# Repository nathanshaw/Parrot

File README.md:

# Parrot
Repo for housing everything Parrot Bot. A mechatronic creature which borrows rhythmic motifs from the sonic environment to playback on a host of actuators.

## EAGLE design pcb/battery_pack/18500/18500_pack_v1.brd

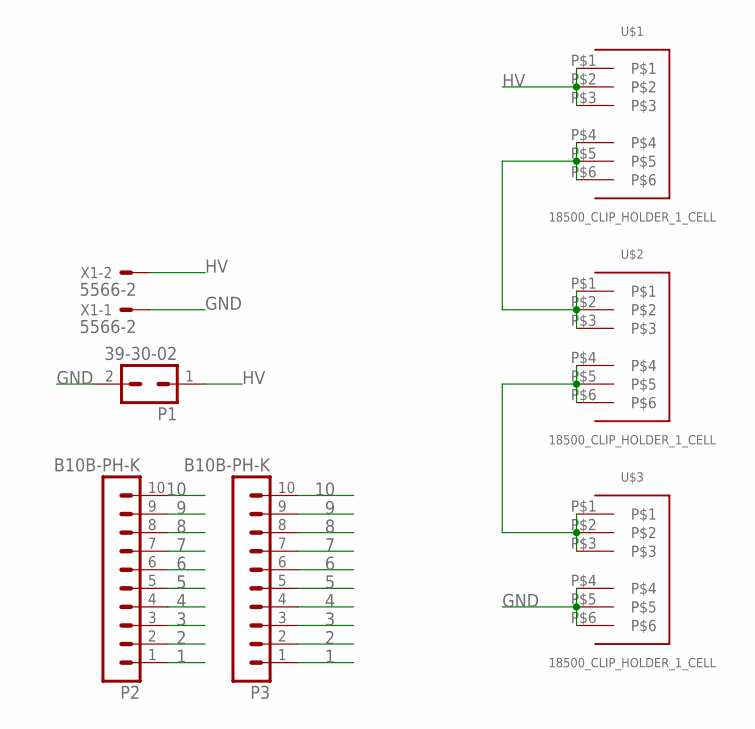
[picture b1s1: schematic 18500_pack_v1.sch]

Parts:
P1: 39-30-02; 39-30-?02?
P2, P3: B10B-PH-K
U$1, U$2, U$3: 18500_CLIP_HOLDER_1_CELL; 3PINBATTERY_CLIP_1_CELL_18500
X1: 5566-2

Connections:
1: P2.1, P3.1
2: P2.2, P3.2
3: P2.3, P3.3
4: P2.4, P3.4
5: P2.5, P3.5
6: P2.6, P3.6
7: P2.7, P3.7
8: P2.8, P3.8
9: P2.9, P3.9
10: P2.10, P3.10
GND: P1.2, U$3.P$4, U$3.P$5, U$3.P$6, X1.1
HV: P1.1, U$1.P$1, U$1.P$2, U$1.P$3, X1.2
unnamed: U$1.P$4, U$1.P$5, U$1.P$6, U$2.P$1, U$2.P$2, U$2.P$3
unnamed: U$2.P$4, U$2.P$5, U$2.P$6, U$3.P$1, U$3.P$2, U$3.P$3

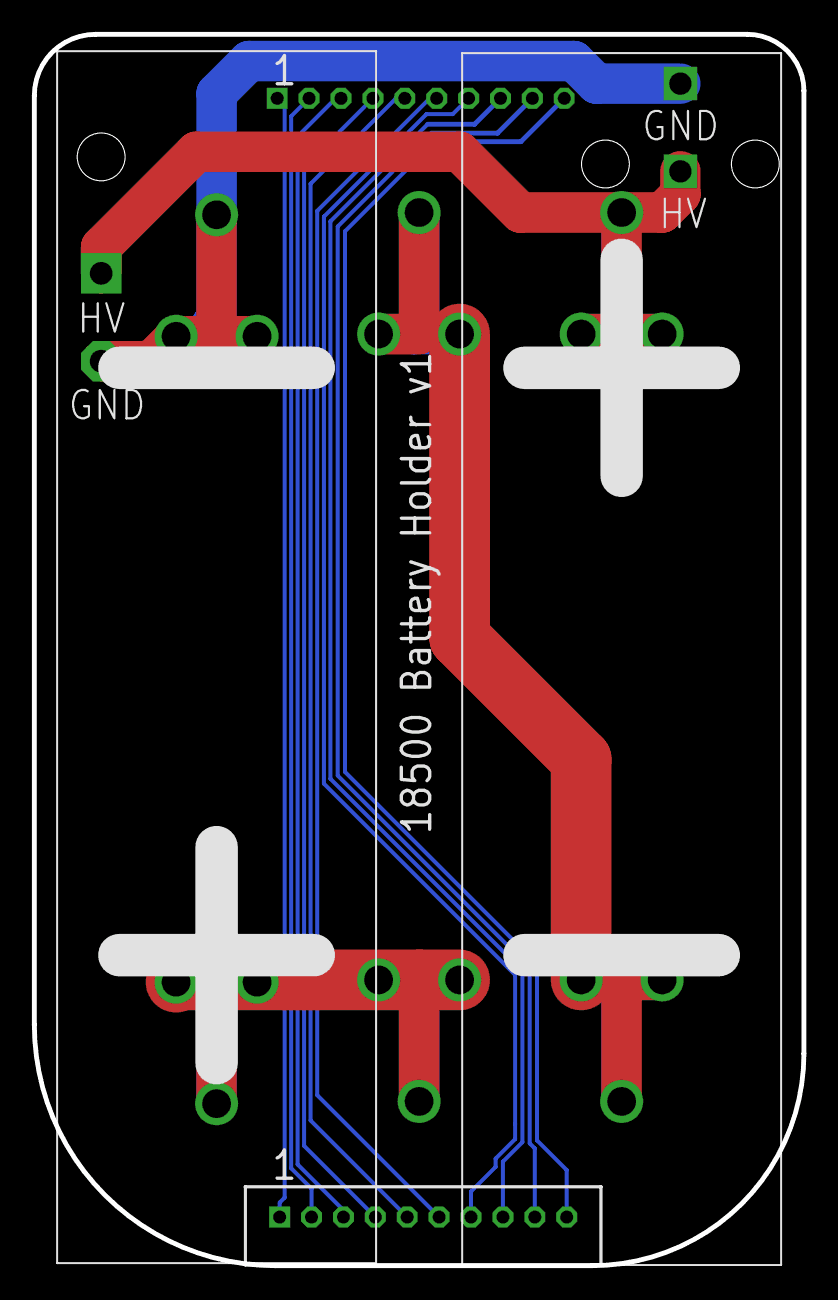
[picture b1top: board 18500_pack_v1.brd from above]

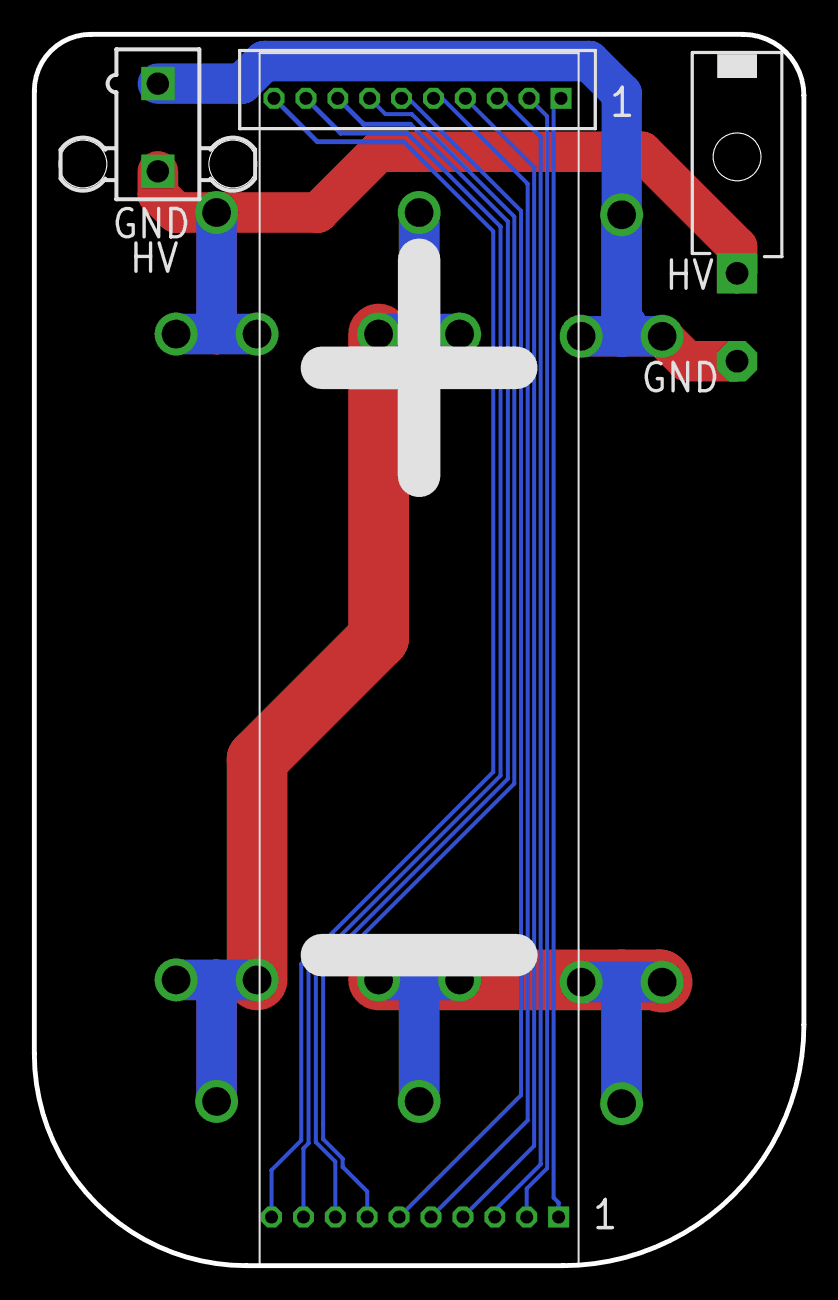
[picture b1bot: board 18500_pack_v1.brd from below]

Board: 2 copper layers, 48.3 x 77.2 mm, 7 parts (4 on the bottom side), 14 nets.

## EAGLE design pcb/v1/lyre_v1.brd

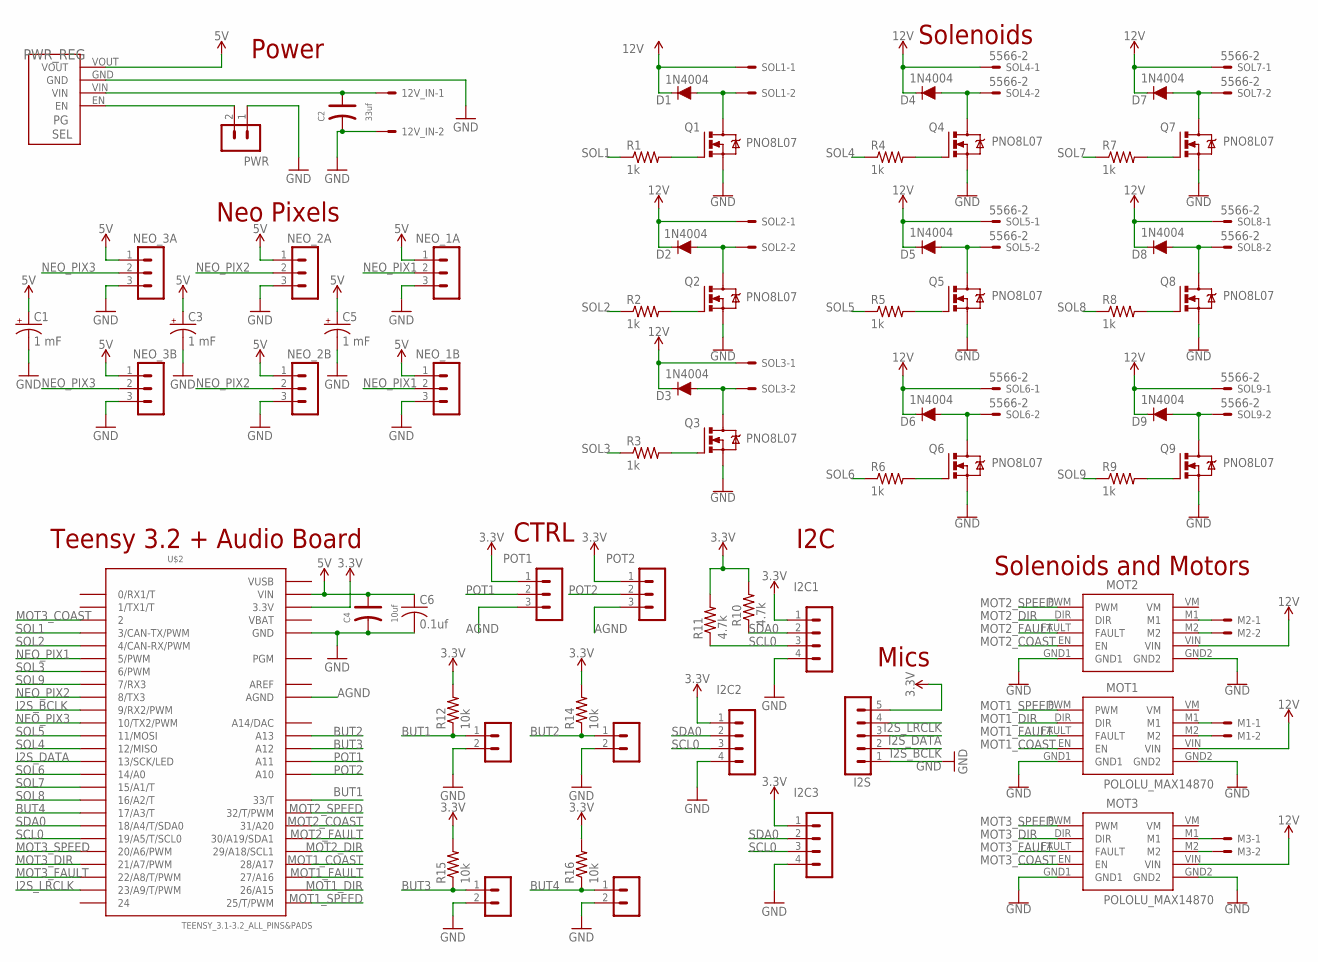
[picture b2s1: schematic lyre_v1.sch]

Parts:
12V_IN: 5566-2
BUT1, BUT2, BUT3, BUT4: B2B-PH-K
C1, C3, C5: 1 mF; UD-10X10_NICHICON
C2: 33uf; PC-D5.3MM
C4: 10uf; PC-D5.3MM
C6: 0.1uf; C2012
D1, D2, D3, D4, D5, D6, D7, D8, D9: 1N4004; DIOAD1138W86L465D235B
I2C1, I2C2, I2C3: B4B-PH-K
I2S: B5B-PH-K
M1, M2, M3: 5566-2
MOT1, MOT2, MOT3: POLOLU_MAX14870
NEO_1A, NEO_1B, NEO_2A, NEO_2B, NEO_3A, NEO_3B: B3B-PH-K
POT1, POT2: B3B-PH-K
PWR: B2B-PH-K
PWR_REG: S9V11F5S6CMA_MISSINIG_PINS; S9V11F3S5CMA_MISSING_PINS
Q1, Q2, Q3, Q4, Q5, Q6, Q7, Q8, Q9: PNO8L07; TO220BV
R1, R2, R3, R4, R5, R6, R7, R8, R9: 1k; R0805
R10, R11: 4.7k; R0805
R12, R14, R15, R16: 10k; R0805
SOL1, SOL2, SOL3, SOL4, SOL5, SOL6, SOL7, SOL8, SOL9: 5566-2
U$2: TEENSY_3.1-3.2_ALL_PINS&PADS; TEENSY_3.0-3.2_ALL_PINS_&_PADS

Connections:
3.3V: I2C1.1, I2C2.1, I2C3.1, I2S.5, POT1.1, POT2.1, R10.2, R11.2, R12.2, R14.2, R15.2, R16.2, U$2.3.3V, U$2.3.3V1 (3.3V), U$2.3.3V2 (3.3V)
5V: C1.+, C3.+, C4.+, C5.+, C6.1, NEO_1A.1, NEO_1B.1, NEO_2A.1, NEO_2B.1, NEO_3A.1, NEO_3B.1, PWR_REG.VOUT, U$2.VIN
12V: 12V_IN.1, C2.+, D1.2 (C), D2.2 (C), D3.2 (C), D4.2 (C), D5.2 (C), D6.2 (C), D7.2 (C), D8.2 (C), D9.2 (C), MOT1.VIN, MOT2.VIN, MOT3.VIN, PWR_REG.VIN, SOL1.1, SOL2.1, SOL3.1, SOL4.1, SOL5.1, SOL6.1, SOL7.1, SOL8.1, SOL9.1
AGND: POT1.3, POT2.3, U$2.AGND
AREF: U$2.AREF
BUT1: BUT1.1, R12.1, U$2.33 (33/T)
BUT2: BUT2.1, R14.1, U$2.A13
BUT3: BUT3.1, R15.1, U$2.A12
BUT4: BUT4.1, R16.1, U$2.17/A3 (17/A3/T)
GND: 12V_IN.2, BUT1.2, BUT2.2, BUT3.2, BUT4.2, C1.-, C2.-, C3.-, C4.-, C5.-, C6.2, I2C1.4, I2C2.4, I2C3.4, I2S.1, MOT1.GND1, MOT1.GND2, MOT2.GND1, MOT2.GND2, MOT3.GND1, MOT3.GND2, NEO_1A.3, NEO_1B.3, NEO_2A.3, NEO_2B.3, NEO_3A.3, NEO_3B.3, PWR.1, PWR_REG.GND, Q1.S, Q2.S, Q3.S, Q4.S, Q5.S, Q6.S, Q7.S, Q8.S, Q9.S, U$2.GND, U$2.GND1 (GND), U$2.GND2 (GND)
I2S_BCLK: I2S.2, U$2.9 (9/RX2/PWM)
I2S_DATA: I2S.3, U$2.13 (13/SCK/LED)
I2S_LRCLK: I2S.4, U$2.23/A9 (23/A9/T/PWM)
MOT1_COAST: MOT1.EN, U$2.28 (28/A17)
MOT1_DIR: MOT1.DIR, U$2.26 (26/A15)
MOT1_FAULT: MOT1.FAULT, U$2.27 (27/A16)
MOT1_SPEED: MOT1.PWM, U$2.25 (25/T/PWM)
MOT2_COAST: MOT2.EN, U$2.31 (31/A20)
MOT2_DIR: MOT2.DIR, U$2.29 (29/A18/SCL1)
MOT2_FAULT: MOT2.FAULT, U$2.30 (30/A19/SDA1)
MOT2_SPEED: MOT2.PWM, U$2.32 (32/T/PWM)
MOT3_COAST: MOT3.EN, U$2.2
MOT3_DIR: MOT3.DIR, U$2.21/A7 (21/A7/PWM)
MOT3_FAULT: MOT3.FAULT, U$2.22/A8 (22/A8/T/PWM)
MOT3_SPEED: MOT3.PWM, U$2.20/A6 (20/A6/PWM)
unnamed: Q5.G, R5.2
unnamed: D5.1 (A), Q5.D, SOL5.2
unnamed: M1.2, MOT1.M2
unnamed: Q6.G, R6.2
unnamed: Q2.G, R2.2
unnamed: D6.1 (A), Q6.D, SOL6.2
unnamed: D2.1 (A), Q2.D, SOL2.2
unnamed: M1.1, MOT1.M1
unnamed: PWR.2, PWR_REG.EN
unnamed: Q3.G, R3.2
unnamed: D3.1 (A), Q3.D, SOL3.2
unnamed: Q4.G, R4.2
unnamed: D4.1 (A), Q4.D, SOL4.2
unnamed: M3.2, MOT3.M2
unnamed: M3.1, MOT3.M1
unnamed: Q7.G, R7.2
unnamed: D7.1 (A), Q7.D, SOL7.2
unnamed: Q8.G, R8.2
unnamed: D8.1 (A), Q8.D, SOL8.2
unnamed: Q9.G, R9.2
unnamed: D9.1 (A), Q9.D, SOL9.2
unnamed: Q1.G, R1.2
unnamed: D1.1 (A), Q1.D, SOL1.2
unnamed: M2.2, MOT2.M2
unnamed: M2.1, MOT2.M1
NEO_PIX1: NEO_1A.2, NEO_1B.2, U$2.5 (5/PWM)
NEO_PIX2: NEO_2A.2, NEO_2B.2, U$2.8 (8/TX3)
NEO_PIX3: NEO_3A.2, NEO_3B.2, U$2.10 (10/TX2/PWM)
POT1: POT1.2, U$2.A11
POT2: POT2.2, U$2.A10
SCL0: I2C1.3, I2C2.3, I2C3.3, R11.1, U$2.19/A5 (19/A5/T/SCL0)
SDA0: I2C1.2, I2C2.2, I2C3.2, R10.1, U$2.18/A4 (18/A4/T/SDA0)
SOL1: R1.1, U$2.3 (3/CAN-TX/PWM)
SOL2: R2.1, U$2.4 (4/CAN-RX/PWM)
SOL3: R3.1, U$2.6 (6/PWM)
SOL4: R4.1, U$2.12 (12/MISO)
SOL5: R5.1, U$2.11 (11/MOSI)
SOL6: R6.1, U$2.14/A0
SOL7: R7.1, U$2.15/A1 (15/A1/T)
SOL8: R8.1, U$2.16/A2 (16/A2/T)
SOL9: R9.1, U$2.7 (7/RX3)
VBAT: U$2.VBAT
VUSB: U$2.VUSB

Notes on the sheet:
Neo Pixels
I2C
Solenoids and Motors
Teensy 3.2 + Audio Board
Mics
Power
CTRL
Solenoids

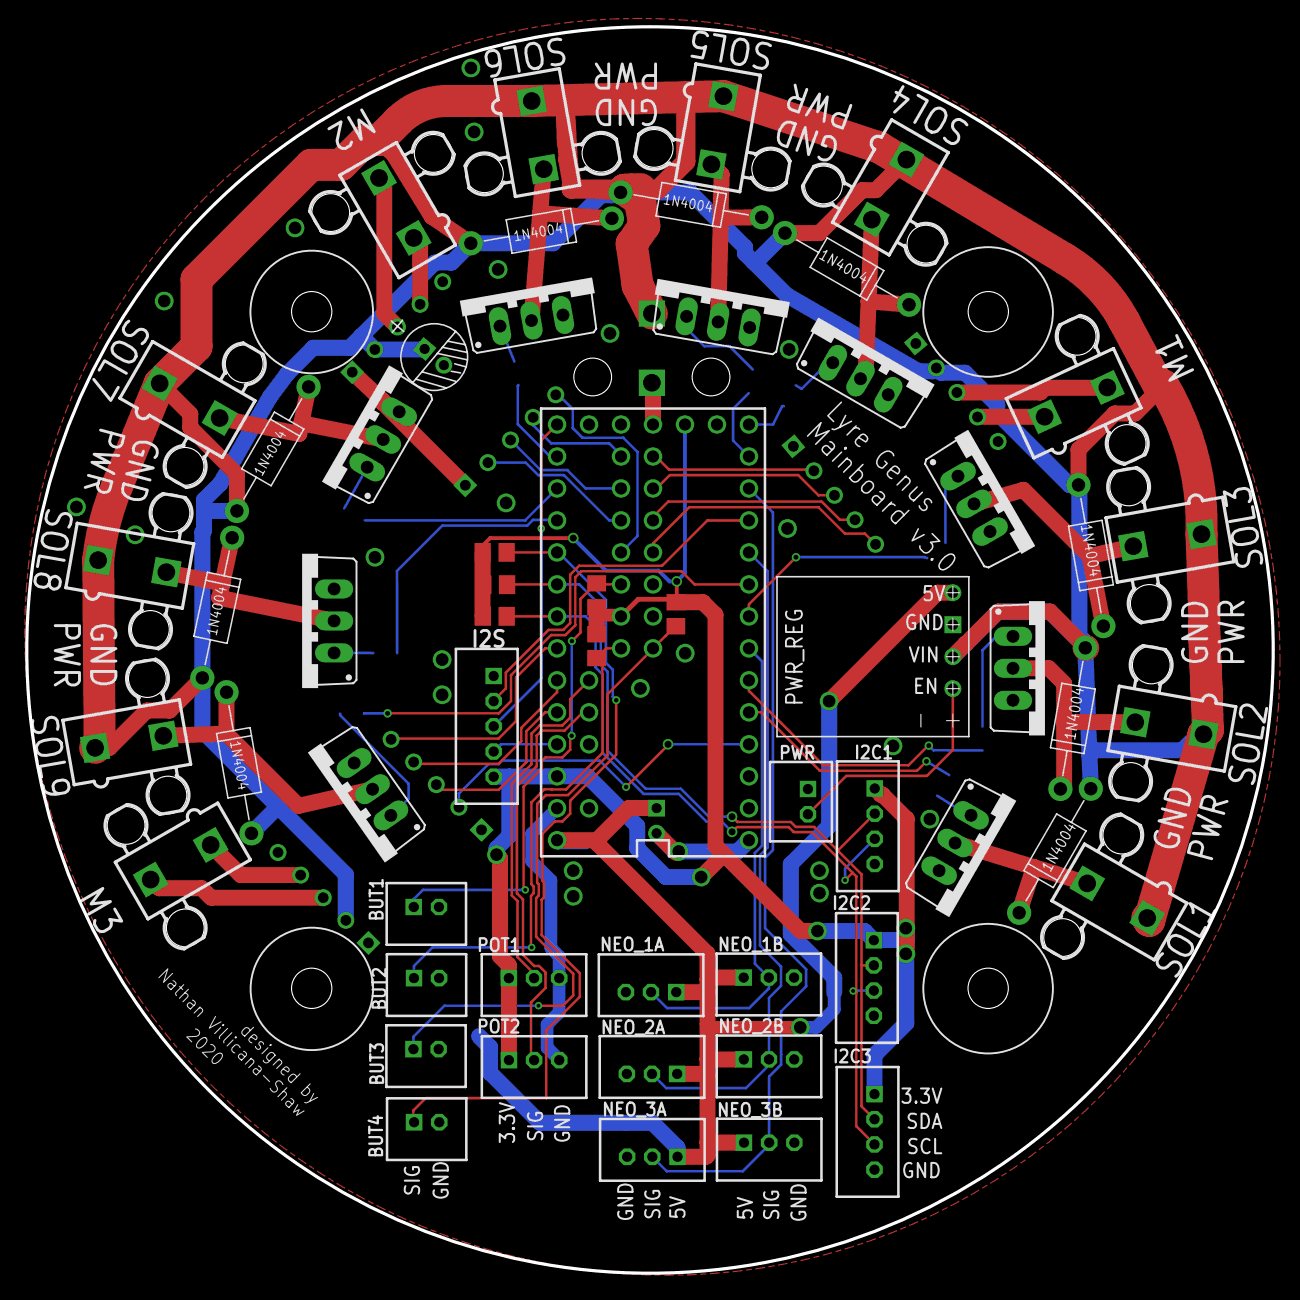
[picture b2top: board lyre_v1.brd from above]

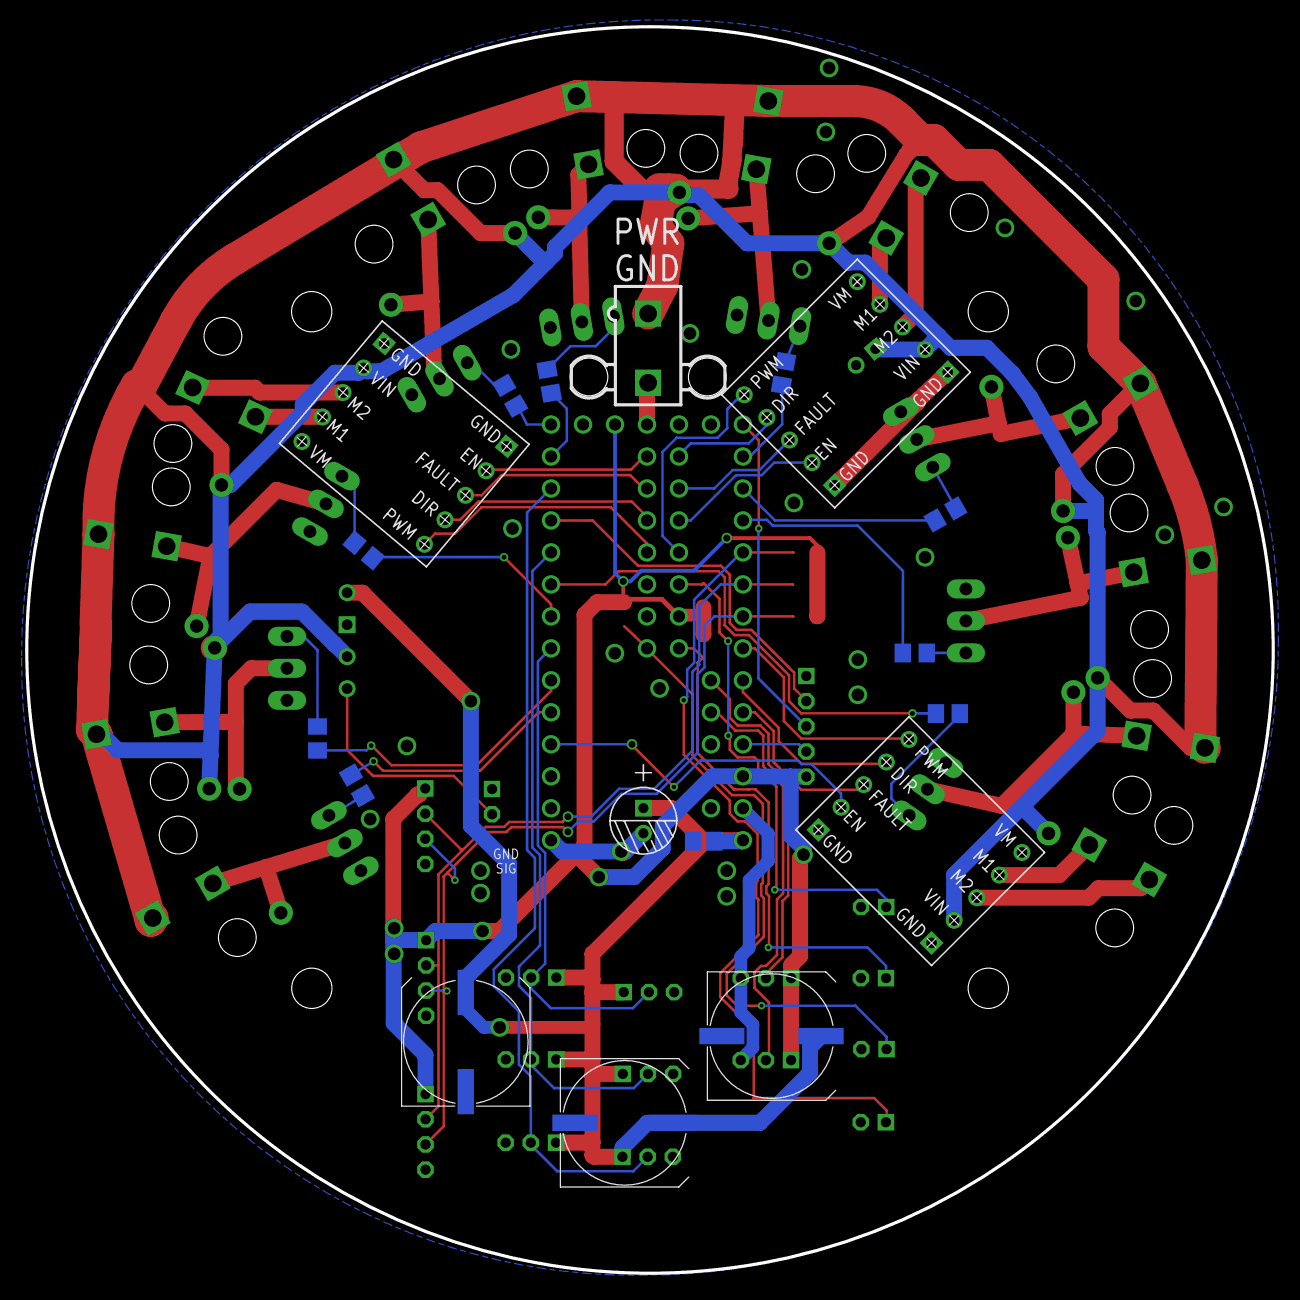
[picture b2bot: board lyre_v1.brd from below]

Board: 2 copper layers, 99.0 x 99.0 mm, 74 parts (18 on the bottom side), 65 nets.

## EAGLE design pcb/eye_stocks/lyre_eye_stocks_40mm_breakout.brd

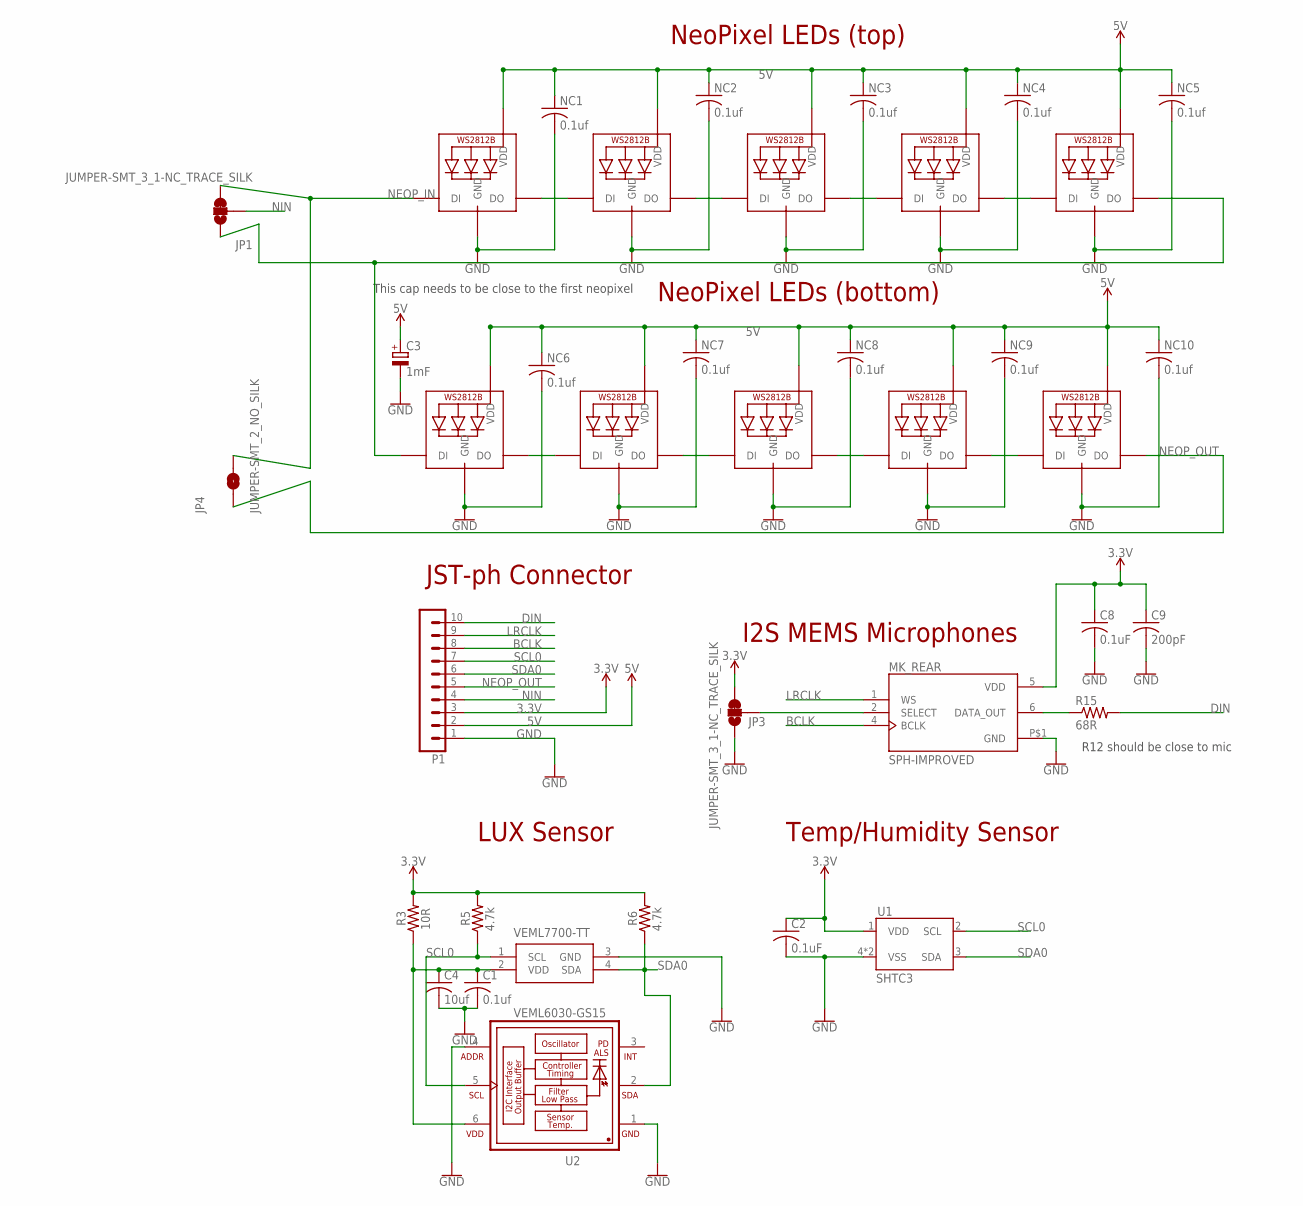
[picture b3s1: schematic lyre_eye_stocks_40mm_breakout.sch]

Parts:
C1: 0.1uf; C0805
C2, C8: 0.1uF; C0805
C3: 1mF; 153CLV-1012
C4: 10uf; C0805
C9: 200pF; C0805
JP1, JP3: JUMPER-SMT_3_1-NC_TRACE_SILK; SMT-JUMPER_3_1-NC_TRACE_SILK
JP4: JUMPER-SMT_2_NO_SILK; SMT-JUMPER_2_NO_SILK
MK_REAR: SPH-IMPROVED; MIC_SPH0645LM4H-B_LARGER_RING
NC1, NC2, NC3, NC4, NC5, NC6, NC7, NC8, NC9, NC10: 0.1uf; C0805
NEO_01, NEO_02, NEO_03, NEO_04, NEO_05, NEO_06, NEO_07, NEO_08, NEO_09, NEO_10: WS2812; WS2812B
P1: B10B-PH-K
R3: 10R; R0805
R5, R6: 4.7k; R0805
R15: 68R; R0805
U1: SHTC3
U2: VEML6030-GS15; VISHAY_VEML6030_2X2X0.87
VEML_F: VEML7700-TT; VEML7700

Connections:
3.3V: C2.1, C8.1, C9.1, JP3.3, MK_REAR.5 (VDD), P1.3, R3.2, R5.2, R6.2, U1.1 (VDD)
5V: C3.+, NC1.1, NC2.1, NC3.1, NC4.1, NC5.1, NC6.1, NC7.1, NC8.1, NC9.1, NC10.1, NEO_01.1-VDD (VDD), NEO_02.1-VDD (VDD), NEO_03.1-VDD (VDD), NEO_04.1-VDD (VDD), NEO_05.1-VDD (VDD), NEO_06.1-VDD (VDD), NEO_07.1-VDD (VDD), NEO_08.1-VDD (VDD), NEO_09.1-VDD (VDD), NEO_10.1-VDD (VDD), P1.2
BCLK: MK_REAR.4 (BCLK), P1.8
DIN: P1.10, R15.2
GND: C1.2, C2.2, C3.-, C4.2, C8.2, C9.2, JP3.1, MK_REAR.P$1 (GND), NC1.2, NC2.2, NC3.2, NC4.2, NC5.2, NC6.2, NC7.2, NC8.2, NC9.2, NC10.2, NEO_01.3-GND (GND), NEO_02.3-GND (GND), NEO_03.3-GND (GND), NEO_04.3-GND (GND), NEO_05.3-GND (GND), NEO_06.3-GND (GND), NEO_07.3-GND (GND), NEO_08.3-GND (GND), NEO_09.3-GND (GND), NEO_10.3-GND (GND), P1.1, U1.4 (VSS), U1.5 (VSS), U2.1 (GND), U2.4 (ADDR), VEML_F.3 (GND)
LRCLK: MK_REAR.1 (WS), P1.9
unnamed: C1.1, C4.1, R3.1, U2.6 (VDD), VEML_F.2 (VDD)
unnamed: JP1.1, NEO_05.2-DOUT (DO), NEO_06.4-DIN (DI)
unnamed: NEO_02.2-DOUT (DO), NEO_03.4-DIN (DI)
unnamed: NEO_09.2-DOUT (DO), NEO_10.4-DIN (DI)
unnamed: JP3.2, MK_REAR.2 (SELECT)
unnamed: NEO_07.2-DOUT (DO), NEO_08.4-DIN (DI)
unnamed: NEO_04.2-DOUT (DO), NEO_05.4-DIN (DI)
unnamed: NEO_08.2-DOUT (DO), NEO_09.4-DIN (DI)
unnamed: NEO_03.2-DOUT (DO), NEO_04.4-DIN (DI)
unnamed: MK_REAR.6 (DATA_OUT), R15.1
NEOP_IN: JP1.3, JP4.2, NEO_01.4-DIN (DI)
NEOP_OUT: JP4.1, NEO_10.2-DOUT (DO), P1.5
NEO_P1: NEO_01.2-DOUT (DO), NEO_02.4-DIN (DI)
NEO_P2: NEO_06.2-DOUT (DO), NEO_07.4-DIN (DI)
NIN: JP1.2, P1.4
SCL0: P1.7, R5.1, U1.2 (SCL), U2.5 (SCL), VEML_F.1 (SCL)
SDA0: P1.6, R6.1, U1.3 (SDA), U2.2 (SDA), VEML_F.4 (SDA)

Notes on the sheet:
I2S MEMS Microphones
LUX Sensor
NeoPixel LEDs (top)
4.7k
R12 should be close to mic
10R
This cap needs to be close to the first neopixel
Temp/Humidity Sensor
NeoPixel LEDs (bottom)
JST-ph Connector

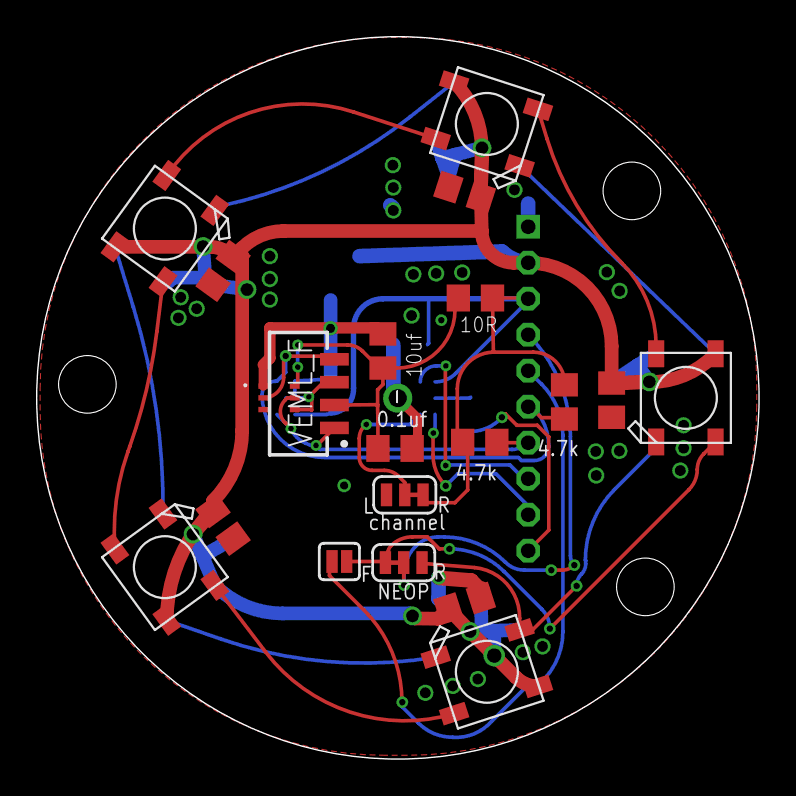
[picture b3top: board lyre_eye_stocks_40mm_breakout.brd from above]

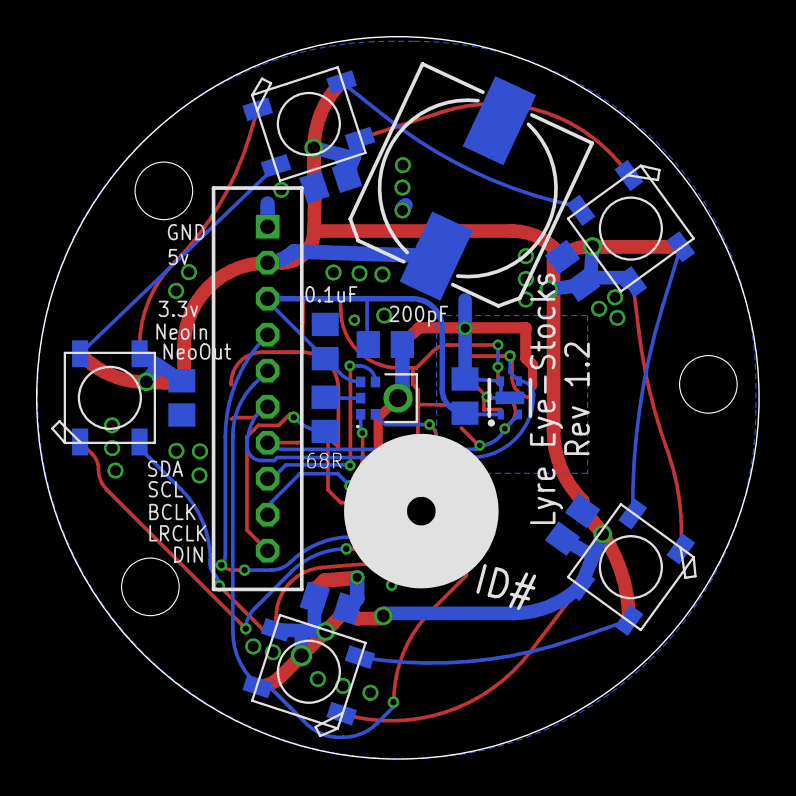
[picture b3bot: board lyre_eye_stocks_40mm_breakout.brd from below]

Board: 2 copper layers, 40.1 x 40.1 mm, 38 parts (18 on the bottom side), 23 nets.

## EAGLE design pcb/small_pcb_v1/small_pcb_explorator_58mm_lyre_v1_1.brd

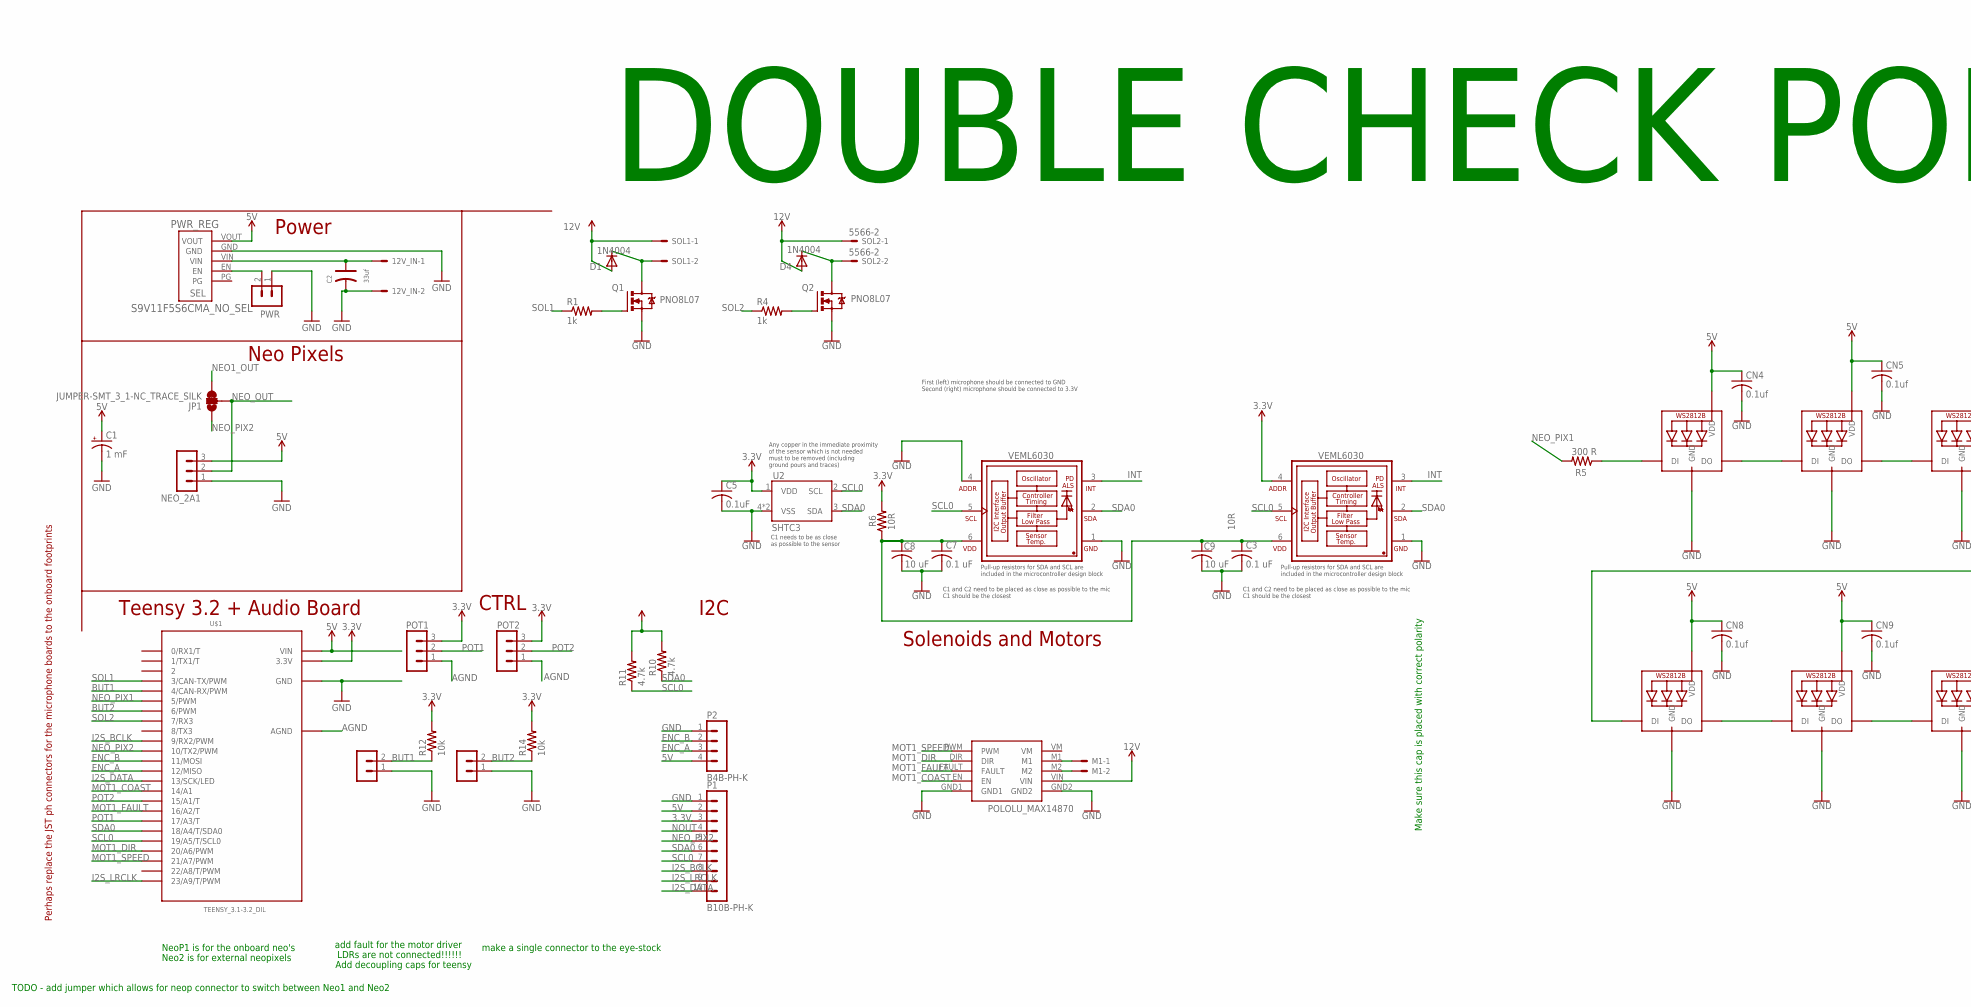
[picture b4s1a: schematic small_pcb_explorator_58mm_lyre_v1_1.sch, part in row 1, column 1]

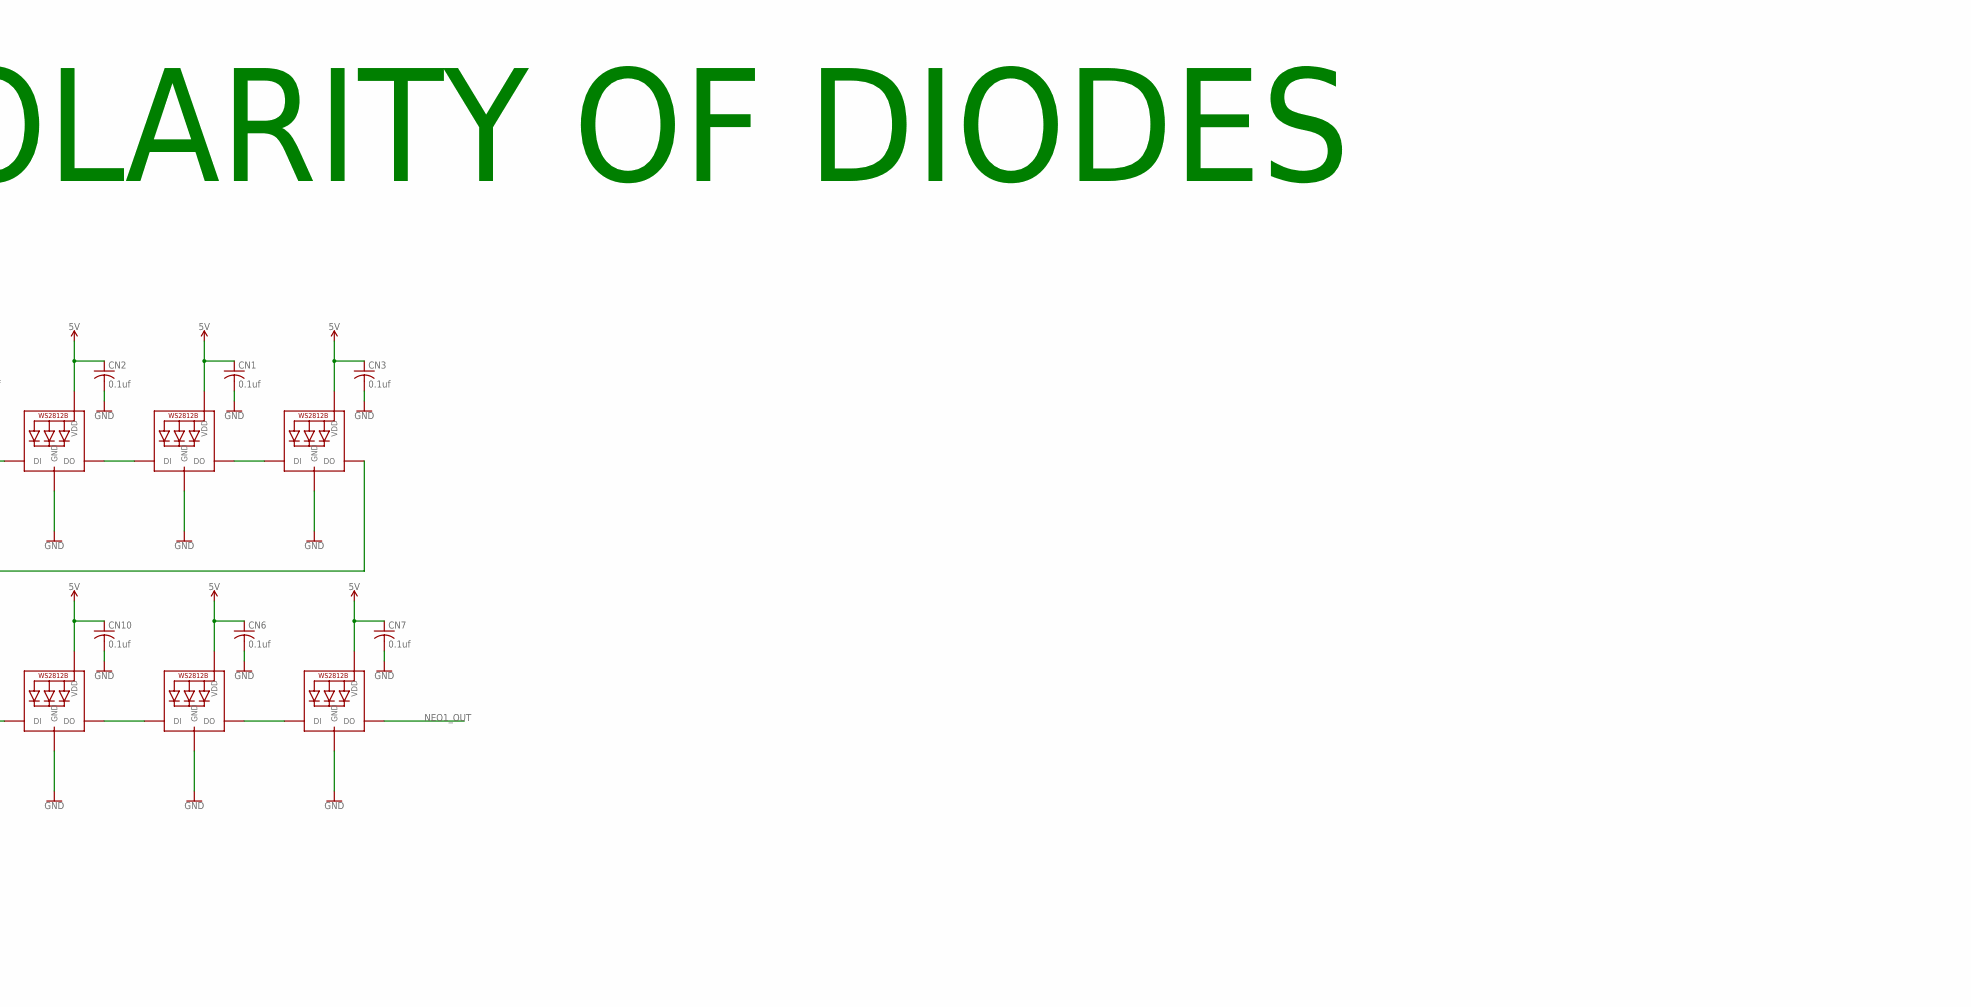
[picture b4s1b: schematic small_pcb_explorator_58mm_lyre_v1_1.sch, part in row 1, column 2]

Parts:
12V_IN: 5566-2
BUT1, BUT2: B2B-PH-K
C1: 1 mF; UD-10X10_NICHICON
C2: 33uf; PC-D5.3MM
C3, C7: 0.1 uF; C0805
C5: 0.1uF; C0805
C8, C9: 10 uF; C0805
CN1, CN2, CN3, CN4, CN5, CN6, CN7, CN8, CN9, CN10: 0.1uf; C0805K
D1, D4: 1N4004; DIODE_DO35-7
JP1: JUMPER-SMT_3_1-NC_TRACE_SILK; SMT-JUMPER_3_1-NC_TRACE_SILK
M1: 5566-2
MOT1: POLOLU_MAX14870
NEO1, NEO2, NEO3, NEO4, NEO5, NEO6, NEO7, NEO8, NEO9, NEO10: WS2812B5050; WS2812B
NEO_2A1: B3B-PH-K
P1: B10B-PH-K
P2: B4B-PH-K
POT1, POT2: B3B-PH-K
PWR: B2B-PH-K
PWR_REG: S9V11F5S6CMA_NO_SEL; S9V11F3S5CMA_NO_SEL
Q1, Q2: PNO8L07; TO220BV
R1, R4: 1k; R0805
R5: 300 R; R0805
R6: 10 R; R0805
R10, R11: 4.7k; R0805
R12, R14: 10k; R0805
SOL1, SOL2: 5566-2
U2: SHTC3
U$1: TEENSY_3.1-3.2_DIL; TEENSY_3.0-3.2&LC_DIL
VMEL1, VMEL2: VEML6030; VISHAY_VEML6030_2X2X0.87

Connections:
3.3V: C5.1, P1.3, POT1.3, POT2.3, R6.2, R10.2, R11.2, R12.2, R14.2, U2.1 (VDD), U$1.3.3V, VMEL2.4 (ADDR)
5V: C1.+, CN1.1, CN2.1, CN3.1, CN4.1, CN5.1, CN6.1, CN7.1, CN8.1, CN9.1, CN10.1, NEO1.1-VDD (VDD), NEO2.1-VDD (VDD), NEO3.1-VDD (VDD), NEO4.1-VDD (VDD), NEO5.1-VDD (VDD), NEO6.1-VDD (VDD), NEO7.1-VDD (VDD), NEO8.1-VDD (VDD), NEO9.1-VDD (VDD), NEO10.1-VDD (VDD), NEO_2A1.3, P1.2, P2.4, PWR_REG.VOUT, U$1.VIN
12V: 12V_IN.1, C2.+, D1.A (C), D4.A (C), MOT1.VIN, PWR_REG.VIN, SOL1.1, SOL2.1
AGND: POT1.1, POT2.1, U$1.AGND
BUT1: BUT1.2, R12.1, U$1.4 (4/CAN-RX/PWM)
BUT2: BUT2.2, R14.1, U$1.6 (6/PWM)
ENC_A: P2.3, U$1.12 (12/MISO)
ENC_B: P2.2, U$1.11 (11/MOSI)
GND: 12V_IN.2, BUT1.1, BUT2.1, C1.-, C2.-, C3.2, C5.2, C7.2, C8.2, C9.2, CN1.2, CN2.2, CN3.2, CN4.2, CN5.2, CN6.2, CN7.2, CN8.2, CN9.2, CN10.2, MOT1.GND1, MOT1.GND2, NEO1.3-GND (GND), NEO2.3-GND (GND), NEO3.3-GND (GND), NEO4.3-GND (GND), NEO5.3-GND (GND), NEO6.3-GND (GND), NEO7.3-GND (GND), NEO8.3-GND (GND), NEO9.3-GND (GND), NEO10.3-GND (GND), NEO_2A1.1, P1.1, P2.1, PWR.1, PWR_REG.GND, Q1.S, Q2.S, U2.4 (VSS), U2.5 (VSS), U$1.GND, VMEL1.1 (GND), VMEL1.4 (ADDR), VMEL2.1 (GND)
I2S_BCLK: P1.8, U$1.9 (9/RX2/PWM)
I2S_DATA: P1.10, U$1.13 (13/SCK/LED)
I2S_LRCLK: P1.9, U$1.23/A9 (23/A9/T/PWM)
INT: VMEL1.3 (INT), VMEL2.3 (INT)
MOT1_COAST: MOT1.EN, U$1.14/A0 (14/A1)
MOT1_DIR: MOT1.DIR, U$1.20/A6 (20/A6/PWM)
MOT1_FAULT: MOT1.FAULT, U$1.16/A2 (16/A2/T)
MOT1_SPEED: MOT1.PWM, U$1.21/A7 (21/A7/PWM)
unnamed: NEO4.2-DOUT (DO), NEO5.4-DIN (DI)
unnamed: NEO1.4-DIN (DI), NEO5.2-DOUT (DO)
unnamed: M1.2, MOT1.M2
unnamed: NEO1.2-DOUT (DO), NEO2.4-DIN (DI)
unnamed: NEO2.2-DOUT (DO), NEO3.4-DIN (DI)
unnamed: NEO3.2-DOUT (DO), NEO8.4-DIN (DI)
unnamed: C3.1, C7.1, C8.1, C9.1, R6.1, VMEL1.6 (VDD), VMEL2.6 (VDD)
unnamed: NEO4.4-DIN (DI), R5.1
unnamed: M1.1, MOT1.M1
unnamed: PWR.2, PWR_REG.EN
unnamed: NEO8.2-DOUT (DO), NEO9.4-DIN (DI)
unnamed: NEO9.2-DOUT (DO), NEO10.4-DIN (DI)
unnamed: Q2.G, R4.2
unnamed: D4.C (A), Q2.D, SOL2.2
unnamed: NEO6.4-DIN (DI), NEO10.2-DOUT (DO)
unnamed: NEO6.2-DOUT (DO), NEO7.4-DIN (DI)
unnamed: Q1.G, R1.2
unnamed: D1.C (A), Q1.D, SOL1.2
NEO1_OUT: JP1.3, NEO7.2-DOUT (DO)
NEO_OUT: JP1.2, NEO_2A1.2
NEO_PIX1: R5.2, U$1.5 (5/PWM)
NEO_PIX2: JP1.1, P1.5, U$1.10 (10/TX2/PWM)
NOUT: P1.4
POT1: POT1.2, U$1.17/A3 (17/A3/T)
POT2: POT2.2, U$1.15/A1 (15/A1/T)
SCL0: P1.7, R11.1, U2.2 (SCL), U$1.19/A5 (19/A5/T/SCL0), VMEL1.5 (SCL), VMEL2.5 (SCL)
SDA0: P1.6, R10.1, U2.3 (SDA), U$1.18/A4 (18/A4/T/SDA0), VMEL1.2 (SDA), VMEL2.2 (SDA)
SOL1: R1.1, U$1.3 (3/CAN-TX/PWM)
SOL2: R4.1, U$1.7 (7/RX3)

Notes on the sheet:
Neo Pixels
I2C
Solenoids and Motors
Teensy 3.2 + Audio Board
Power
Make sure this cap is placed with correct polarity
CTRL
add fault for the motor driver
LDRs are not connected!!!!!!
Add decoupling caps for teensy
Perhaps replace the JST ph connectors for the microphone boards to the onboard footprints
make a single connector to the eye-stock
10R
First (left) microphone should be connected to GND Second (right) microphone should be connected to 3.3V
C1 and C2 need to be placed as close as possible to the mic C1 should be the closest
Pull-up resistors for SDA and SCL are included in the microcontroller design block
C1 needs to be as close as possible to the sensor
Any copper in the immediate proximity of the sensor which is not needed must to be removed (including ground pours and traces)
NeoP1 is for the onboard neo's
Neo2 is for external neopixels
TODO - add jumper which allows for neop connector to switch between Neo1 and Neo2
DOUBLE CHECK POLARITY OF DIODES

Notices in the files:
parts and their libraries:
con-molex-mini-fit: Copyright (C) 2011, Bob Starr
con-jst-ph: Copyright (C) 2016, Bob Starr
SparkFun-Jumpers: Licensing: Creative Commons ShareAlike 4.0 International - https://creativecommons.org/licenses/by-sa/4.0
